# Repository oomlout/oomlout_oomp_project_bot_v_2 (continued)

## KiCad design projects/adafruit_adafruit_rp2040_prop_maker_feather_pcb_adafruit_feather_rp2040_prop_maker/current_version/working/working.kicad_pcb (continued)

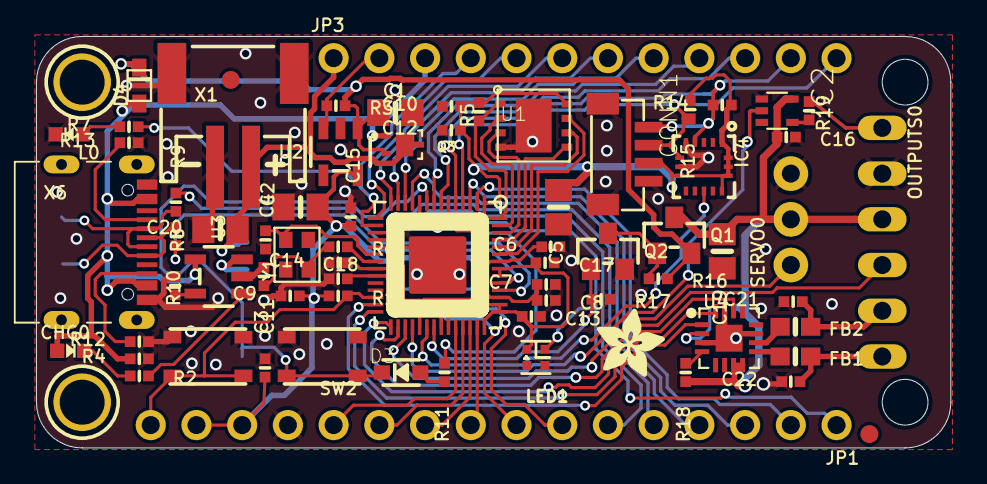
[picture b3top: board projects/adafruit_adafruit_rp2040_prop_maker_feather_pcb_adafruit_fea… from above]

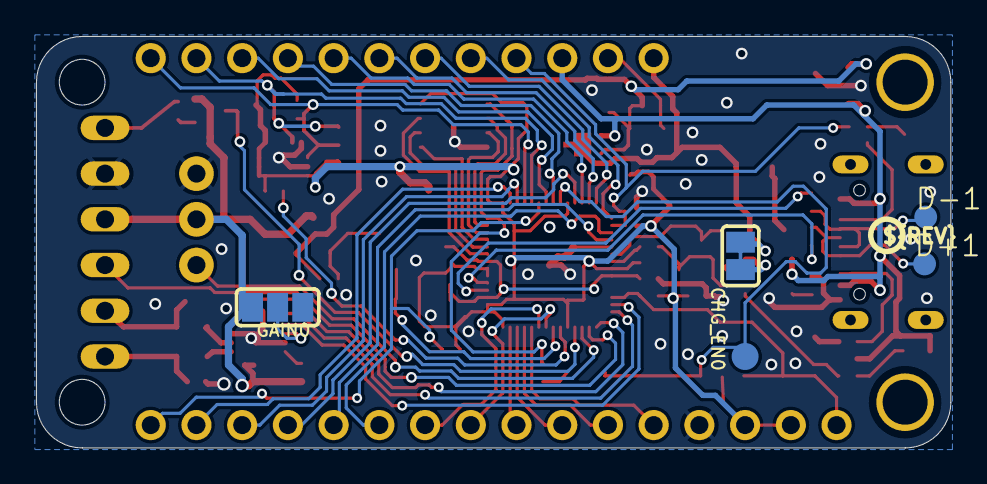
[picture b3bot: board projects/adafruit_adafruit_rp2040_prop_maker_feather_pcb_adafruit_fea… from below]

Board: 2 copper layers, 50.8 x 22.9 mm, 164 parts (51 on the bottom side), 69 nets.

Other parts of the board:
@HOLE0, @HOLE1: (no value)
PLABEL0: PLABEL0
PLABEL1: PLABEL1
PLABEL2: PLABEL2
PLABEL3: PLABEL3
PLABEL4: PLABEL4
PLABEL5: PLABEL5
PLABEL6: PLABEL6
PLABEL7: PLABEL7
PLABEL8: PLABEL8
PLABEL9: PLABEL9
PLABEL10: PLABEL10
PLABEL11: PLABEL11
PLABEL12: PLABEL12
PLABEL13: PLABEL13
PLABEL14: PLABEL14
PLABEL15: PLABEL15
PLABEL16: PLABEL16
PLABEL17: PLABEL17
PLABEL18: PLABEL18
PLABEL19, PLABEL26: PLABEL26
PLABEL21: PLABEL21
PLABEL22: PLABEL22
PLABEL23: PLABEL23
PLABEL24: PLABEL24
PLABEL25: PLABEL25
PLABEL27: PLABEL27
PLABEL28: PLABEL28
PLABEL29: PLABEL29
PLABEL30: PLABEL30
PLABEL31: PLABEL31
PLABEL32: PLABEL32
PLABEL33: PLABEL33
PLABEL36: PLABEL36
PLABEL37: PLABEL37
PLABEL38: PLABEL38
PLABEL39: PLABEL39
PLABEL40: PLABEL40
PLABEL41: PLABEL41
PLABEL42: PLABEL42
PLABEL43: PLABEL43
PLABEL44: PLABEL44
PLABEL45: PLABEL45
PLABEL46: PLABEL46
PLABEL47: PLABEL47
PLABEL48: PLABEL48
PLABEL49: PLABEL49
PLABEL50: PLABEL50
PLABEL51: PLABEL51
PLABEL52: PLABEL52
PLABEL53: PLABEL53
PLABEL54: PLABEL54
PLABEL55: PLABEL55
PLABEL56: PLABEL56
PLABEL57: PLABEL57
PLABEL58: PLABEL58
PLABEL59: PLABEL59
PLABEL60: PLABEL60
PLABEL61: PLABEL61
PLABEL62: PLABEL62
PLABEL63: PLABEL63
PLABEL68: PLABEL68
PLABEL69: PLABEL69
PLABEL70: PLABEL70
PLABEL71: PLABEL71
PLABEL72: PLABEL72
PLABEL73: PLABEL73
PLABEL74: PLABEL74
PLABEL75: PLABEL75
PLABEL76: PLABEL76
PLABEL77: PLABEL77
PLABEL78: PLABEL78
PLABEL79: PLABEL79
PLABEL80: PLABEL80
PLABEL81: PLABEL81
PLABEL82: PLABEL82
PLABEL83: PLABEL83
PLABEL84: PLABEL84
PLABEL85: PLABEL85
PLABEL86: PLABEL86
PLABEL87: PLABEL87
PLABEL88: PLABEL88
PLABEL89: PLABEL89
U$13: PCBFEAT-REV-040
U$42: ADAFRUIT_3.5MM

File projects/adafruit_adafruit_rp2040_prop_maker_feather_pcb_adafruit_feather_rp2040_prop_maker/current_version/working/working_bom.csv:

"Id";"Designator";"Footprint";"Quantity";"Designation";"Supplier and ref";
1;"PLABEL30";"PLABEL30";1;"";;;
2;"R2,R5,R1,R4,R14,R3,R15,R7";"_0402NO";8;"10K";;;
3;"C7,C6,C12,C18,C9,C13,C16,C14";"_0402NO";8;"0.1uF";;;
4;"R6,R11";"_0402NO";2;"1K";;;
5;"U$31,U$32";"MOUNTINGHOLE_2.5_PLATED";2;"MOUNTINGHOLE2.5";;;
6;"C20,C1,C19,C5,C4";"0805-NO";5;"10uF/16V";;;
7;"PLABEL72";"PLABEL72";1;"";;;
8;"U$35,U$34";"FIDUCIAL_1MM";2;"FIDUCIAL_1MM";;;
9;"OUTPUTS0";"1X06_OVAL";1;"TERMINALS";;;
10;"PLABEL13";"PLABEL13";1;"";;;
11;"LED1";"SK6805_1515";1;"WS2812B_SK6805_1515";;;
12;"PLABEL73";"PLABEL73";1;"";;;
13;"R19";"_0402NO";1;"100";;;
14;"PLABEL6";"PLABEL6";1;"";;;
15;"Y1";"CRYSTAL_2.5X2";1;"12MHz/12pF";;;
16;"PLABEL33";"PLABEL33";1;"";;;
17;"U2";"SOT23-5";1;"RT9080-3.3";;;
18;"R16,R17";"_0402NO";2;"100K";;;
19;"PLABEL19,PLABEL26";"PLABEL26";2;"";;;
20;"PLABEL36";"PLABEL36";1;"";;;
21;"PLABEL23";"PLABEL23";1;"";;;
22;"C2,C3";"_0402NO";2;"22pF";;;
23;"C10,C11,C15,C8,C17";"_0402NO";5;"1uF/25V";;;
24;"SERVO0";"1X03_ROUND_76";1;"1x3M";;;
25;"IC1";"QFN56_7MM_REDUCEDEPAD";1;"RP2040_QFN56";;;
26;"R12,R8,R13";"_0402NO";3;"5.1K";;;
27;"PLABEL18";"PLABEL18";1;"";;;
28;"R18";"_0402NO";1;"1M";;;
29;"PLABEL5";"PLABEL5";1;"";;;
30;"@HOLE1,@HOLE0";"";2;"";;;
31;"PLABEL16";"PLABEL16";1;"";;;
32;"PLABEL3";"PLABEL3";1;"";;;
33;"PLABEL4";"PLABEL4";1;"";;;
34;"U3";"SOT23-5";1;"MCP73831T-2ACI/OT";;;
35;"PLABEL27";"PLABEL27";1;"";;;
36;"PLABEL17";"PLABEL17";1;"";;;
37;"IC4";"LGA16_3X3MM";1;"LIS3DH";;;
38;"R10,R9";"_0402NO";2;"22 ohm";;;
39;"C22,C21";"_0402NO";2;"220pF";;;
40;"PLABEL22";"PLABEL22";1;"";;;
41;"U4";"QFN16_3MM";1;"MAX98357A";;;
42;"X6";"USB_C_CUSB31-CFM2AX-01-X";1;"USB Type C";;;
43;"PLABEL71";"PLABEL71";1;"";;;
44;"L0";"CHIPLED_0603_NOOUTLINE";1;"RED";;;
45;"PLABEL21";"PLABEL21";1;"";;;
46;"PLABEL31";"PLABEL31";1;"";;;
47;"PLABEL7";"PLABEL7";1;"";;;
48;"PLABEL12";"PLABEL12";1;"";;;
49;"PLABEL8";"PLABEL8";1;"";;;
50;"Q2";"SOT23-WIDE";1;"C20917";;;
51;"PLABEL9";"PLABEL9";1;"";;;
52;"Q1";"SOT23-WIDE";1;"AO3401";;;
53;"Q3";"DFN2015-3";1;"DMG3415UFY";;;
54;"FB2,FB1";"0603-NO";2;"Ferrite";;;
55;"PLABEL2";"PLABEL2";1;"";;;
56;"PLABEL24";"PLABEL24";1;"";;;
57;"PLABEL11";"PLABEL11";1;"";;;
58;"SW2,SW1";"BTN_RKB2_4.6X2.8";2;"RKB2";;;
59;"U1";"USON8_4X4";1;"8MB QSPI";;;
60;"PLABEL10";"PLABEL10";1;"";;;
61;"PLABEL28";"PLABEL28";1;"";;;
62;"X1";"JSTPH2_BATT";1;"JSTPH";;;
63;"PLABEL29";"PLABEL29";1;"";;;
64;"U$42";"ADAFRUIT_3.5MM";1;"";;;
65;"PLABEL14";"PLABEL14";1;"";;;
66;"CONN1";"JST_SH4_RA";1;"STEMMA_I2C_QTRA";;;
67;"JP3";"1X12_ROUND";1;"";;;
68;"D3";"SOD-323_MINI";1;"1N4148";;;
69;"D4";"SOD-323F";1;"PMEG2020AEA";;;
70;"PLABEL1";"PLABEL1";1;"";;;
71;"IC2";"SC70-5";1;"74AHCT1G125DCK";;;
72;"PLABEL25";"PLABEL25";1;"";;;
73;"JP1";"1X16_ROUND";1;"";;;
74;"PLABEL70";"PLABEL70";1;"";;;
75;"PLABEL32";"PLABEL32";1;"";;;
76;"PLABEL15";"PLABEL15";1;"";;;
77;"PLABEL0";"PLABEL0";1;"";;;
78;"CHG0";"CHIPLED_0603_NOOUTLINE";1;"ORANGE";;;
79;"PLABEL81";"PLABEL81";1;"";;;
80;"PLABEL88";"PLABEL88";1;"";;;
81;"PLABEL47";"PLABEL47";1;"";;;
82;"PLABEL75";"PLABEL75";1;"";;;
83;"PLABEL69";"PLABEL69";1;"";;;
84;"PLABEL50";"PLABEL50";1;"";;;
85;"PLABEL40";"PLABEL40";1;"";;;
86;"PLABEL51";"PLABEL51";1;"";;;
87;"PLABEL42";"PLABEL42";1;"";;;
88;"PLABEL46";"PLABEL46";1;"";;;
89;"PLABEL86";"PLABEL86";1;"";;;
90;"PLABEL60";"PLABEL60";1;"";;;
91;"U$13";"PCBFEAT-REV-040";1;"";;;
92;"D+1,D-1";"B1,27";2;"TPB1,27";;;
93;"PLABEL38";"PLABEL38";1;"";;;
94;"PLABEL58";"PLABEL58";1;"";;;
95;"PLABEL55";"PLABEL55";1;"";;;
96;"PLABEL85";"PLABEL85";1;"";;;
97;"PLABEL59";"PLABEL59";1;"";;;
98;"GAIN0";"SOLDERJUMPER_2WAY_OPEN_NOPASTE";1;"";;;
99;"PLABEL82";"PLABEL82";1;"";;;
100;"PLABEL80";"PLABEL80";1;"";;;
101;"PLABEL57";"PLABEL57";1;"";;;
102;"PLABEL45";"PLABEL45";1;"";;;
103;"PLABEL48";"PLABEL48";1;"";;;
104;"PLABEL52";"PLABEL52";1;"";;;
105;"PLABEL77";"PLABEL77";1;"";;;
106;"TP3";"TESTPOINT_ROUND_1.5MM_NO";1;"";;;
107;"PLABEL43";"PLABEL43";1;"";;;
108;"PLABEL53";"PLABEL53";1;"";;;
109;"PLABEL62";"PLABEL62";1;"";;;
110;"PLABEL83";"PLABEL83";1;"";;;
111;"PLABEL74";"PLABEL74";1;"";;;
112;"PLABEL41";"PLABEL41";1;"";;;
113;"PLABEL56";"PLABEL56";1;"";;;
114;"PLABEL76";"PLABEL76";1;"";;;
115;"PLABEL61";"PLABEL61";1;"";;;
116;"PLABEL78";"PLABEL78";1;"";;;
117;"PLABEL89";"PLABEL89";1;"";;;
118;"PLABEL37";"PLABEL37";1;"";;;
119;"PLABEL68";"PLABEL68";1;"";;;
120;"PLABEL39";"PLABEL39";1;"";;;
121;"PLABEL84";"PLABEL84";1;"";;;
122;"PLABEL54";"PLABEL54";1;"";;;
123;"PLABEL87";"PLABEL87";1;"";;;
124;"PLABEL63";"PLABEL63";1;"";;;
125;"PLABEL79";"PLABEL79";1;"";;;
126;"PLABEL49";"PLABEL49";1;"";;;
127;"PLABEL44";"PLABEL44";1;"";;;
128;"CHG_EN0";"SOLDERJUMPER_CLOSEDWIRE";1;"";;;

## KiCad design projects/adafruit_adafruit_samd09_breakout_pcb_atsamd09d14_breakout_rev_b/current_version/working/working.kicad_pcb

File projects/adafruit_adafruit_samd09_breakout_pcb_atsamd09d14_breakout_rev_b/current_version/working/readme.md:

# adafruit_samd09_breakout_pcb
 
## summary 
* id: adafruit_adafruit_samd09_breakout_pcb_atsamd09d14_breakout_rev_b
* user: adafruit
* name: adafruit_samd09_breakout_pcb
* board: atsamd09d14_breakout_rev_b
* repo: https://github.com/adafruit/Adafruit-SAMD09-Breakout-PCB

* src_file_repo_sch: 
* src_file_repo_sch_link: https://github.com/adafruit/Adafruit-SAMD09-Breakout-PCB/tree/master/
* full details link: https://github.com/oomlout/oomlout_oomp_project_bot_v_2/tree/main/projects/adafruit_adafruit_samd09_breakout_pcb_atsamd09d14_breakout_rev_b/current_version/working  

## schematic  
  
[schematic (pdf)](working_schematic.pdf) 

## pcb  

[board (pdf)](working.pdf)  

## working_bom
| Id | Designator | Footprint | Quantity | Designation | Supplier and ref |  | None | 
| --- | --- | --- | --- | --- | --- | --- | --- | 
| 1 | JP3,JP1 | 1X12_ROUND_76MIL | 2 |  |  |  | [''] | 
| 2 | R4,R5 | 0603-NO | 2 | 10k |  |  | [''] | 
| 3 | U$12 | PCBFEAT-REV-040 | 1 |  |  |  | [''] | 
| 4 | IC1 | QFN24_4MM | 1 | ATSAMD09D14A-MU |  |  | [''] | 
| 5 | D2 | CHIPLED_0805_NOOUTLINE | 1 | GREEN |  |  | [''] | 
| 6 | C2 | 0603-NO | 1 | 0.1uF |  |  | [''] | 
| 7 | C1,C4 | 0805-NO | 2 | 10uF |  |  | [''] | 
| 8 | FID1,FID2 | FIDUCIAL_1MM | 2 | FIDUCIAL" |  |  | [''] | 
| 9 | SW1 | BTN_KMR2_4.6X2.8 | 1 | KMR2 |  |  | [''] | 
| 10 | R1,R2,R3 | 0603-NO | 3 | 1K |  |  | [''] | 
| 11 | D1 | CHIPLED_0805_NOOUTLINE | 1 | RED |  |  | [''] | 
| 12 | U1 | SOT23-5 | 1 | AP2112K |  |  | [''] | 
| 13 | U$7 | SEESAW_LOGO | 1 |  |  |  | [''] | 

## bom_schematic
| Ref | Qnty | Value | Cmp name | Footprint | Description | Vendor | DNP | 
| --- | --- | --- | --- | --- | --- | --- | --- | 
| C1, C4 | 2 | 10uF | CAP_CERAMIC0805-NOOUTLINE | working:0805-NO |  |  |  | 
| C2 | 1 | 0.1uF | CAP_CERAMIC0603_NO | working:0603-NO |  |  |  | 
| D1 | 1 | RED | LED0805_NOOUTLINE | working:CHIPLED_0805_NOOUTLINE |  |  |  | 
| D2 | 1 | GREEN | LED0805_NOOUTLINE | working:CHIPLED_0805_NOOUTLINE |  |  |  | 
| FID1, FID2 | 2 | FIDUCIAL"" | FIDUCIAL{dblquote}{dblquote} | working:FIDUCIAL_1MM |  |  |  | 
| IC1 | 1 | ATSAMD09D14A-MU | ATSAMD09D14A-MU | working:QFN24_4MM |  |  |  | 
| JP1, JP3 | 2 | HEADER-1X1276MIL | HEADER-1X1276MIL | working:1X12_ROUND_76MIL |  |  |  | 
| R1, R2, R3 | 3 | 1K | RESISTOR_0603_NOOUT | working:0603-NO |  |  |  | 
| R4, R5 | 2 | 10k | RESISTOR_0603_NOOUT | working:0603-NO |  |  |  | 
| SW1 | 1 | KMR2 | SWITCH_TACT_SMT4.6X2.8 | working:BTN_KMR2_4.6X2.8 |  |  |  | 
| U1 | 1 | AP2112K | VREG_SOT23-5 | working:SOT23-5 |  |  |  |

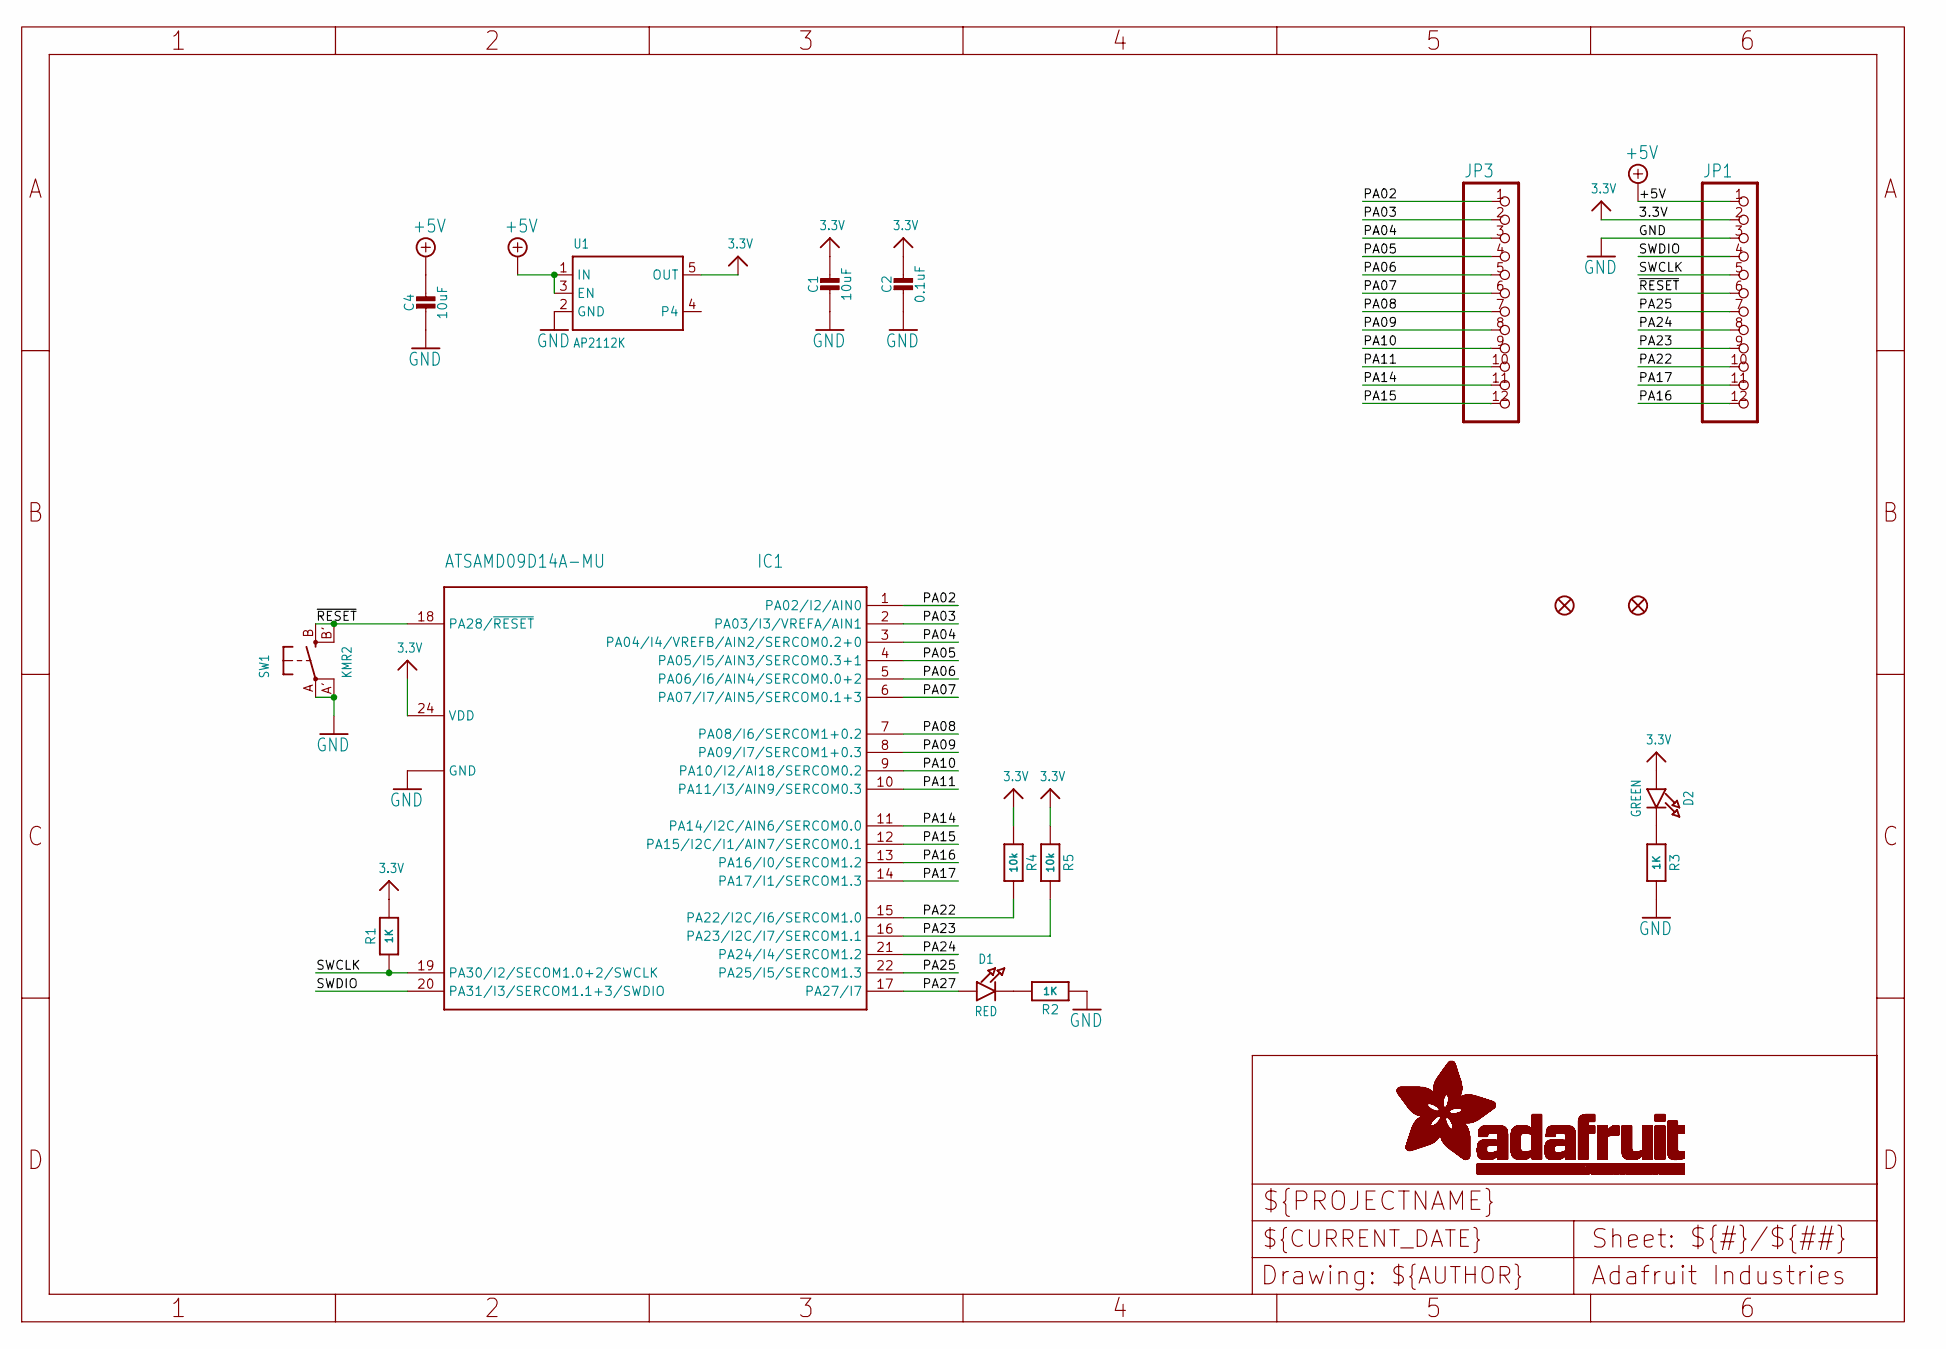
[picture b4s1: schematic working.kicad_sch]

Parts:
C1, C4: 10uF; 0805-NO
C2: 0.1uF; 0603-NO
D1: RED; CHIPLED_0805_NOOUTLINE
D2: GREEN; CHIPLED_0805_NOOUTLINE
FID1, FID2: FIDUCIAL""; FIDUCIAL_1MM
IC1: ATSAMD09D14A-MU; QFN24_4MM
JP1, JP3: HEADER-1X1276MIL; 1X12_ROUND_76MIL
R1, R2, R3: 1K; 0603-NO
R4, R5: 10k; 0603-NO
SW1: KMR2; BTN_KMR2_4.6X2.8
U1: AP2112K; SOT23-5

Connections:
3.3V: C1.1, C2.1, D2.A, IC1.24 (VDD), JP1.2, R1.2, R4.1, R5.1, U1.5 (OUT)
+5V: C4.1, JP1.1, U1.1 (IN), U1.3 (EN)
GND: C1.2, C2.2, C4.2, IC1.23 (GND), IC1.THERM (GND), JP1.3, R2.1, R3.2, SW1.A, SW1.A' (P1), U1.2 (GND)
unnamed: D1.C, R2.2
unnamed: D2.C, R3.1
PA02: IC1.1 (PA02/I2/AIN0), JP3.1
PA03: IC1.2 (PA03/I3/VREFA/AIN1), JP3.2
PA04: IC1.3 (PA04/I4/VREFB/AIN2/SERCOM0.2+0), JP3.3
PA05: IC1.4 (PA05/I5/AIN3/SERCOM0.3+1), JP3.4
PA06: IC1.5 (PA06/I6/AIN4/SERCOM0.0+2), JP3.5
PA07: IC1.6 (PA07/I7/AIN5/SERCOM0.1+3), JP3.6
PA08: IC1.7 (PA08/I6/SERCOM1+0.2), JP3.7
PA09: IC1.8 (PA09/I7/SERCOM1+0.3), JP3.8
PA10: IC1.9 (PA10/I2/AI18/SERCOM0.2), JP3.9
PA11: IC1.10 (PA11/I3/AIN9/SERCOM0.3), JP3.10
PA14: IC1.11 (PA14/I2C/AIN6/SERCOM0.0), JP3.11
PA15: IC1.12 (PA15/I2C/I1/AIN7/SERCOM0.1), JP3.12
PA16: IC1.13 (PA16/I0/SERCOM1.2), JP1.12
PA17: IC1.14 (PA17/I1/SERCOM1.3), JP1.11
PA22: IC1.15 (PA22/I2C/I6/SERCOM1.0), JP1.10, R4.2
PA23: IC1.16 (PA23/I2C/I7/SERCOM1.1), JP1.9, R5.2
PA24: IC1.21 (PA24/I4/SERCOM1.2), JP1.8
PA25: IC1.22 (PA25/I5/SERCOM1.3), JP1.7
PA27: D1.A, IC1.17 (PA27/I7)
SWCLK: IC1.19 (PA30/I2/SECOM1.0+2/SWCLK), JP1.5, R1.1
SWDIO: IC1.20 (PA31/I3/SERCOM1.1+3/SWDIO), JP1.4
~RESET: IC1.18 (PA28/~RESET), JP1.6, SW1.B (S), SW1.B' (S1)

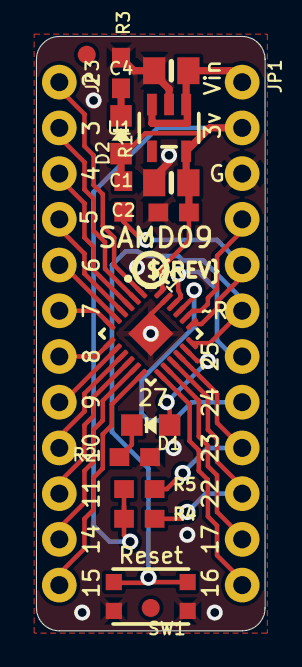
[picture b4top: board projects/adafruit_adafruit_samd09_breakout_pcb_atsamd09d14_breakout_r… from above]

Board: 2 copper layers, 12.7 x 33.0 mm, 19 parts (1 on the bottom side), 27 nets.

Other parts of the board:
U$7: SEESAW_LOGO
U$12: PCBFEAT-REV-040

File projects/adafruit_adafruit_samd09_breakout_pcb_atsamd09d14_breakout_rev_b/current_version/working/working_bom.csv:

"Id";"Designator";"Footprint";"Quantity";"Designation";"Supplier and ref";
1;"JP3,JP1";"1X12_ROUND_76MIL";2;"";;;
2;"R4,R5";"0603-NO";2;"10k";;;
3;"U$12";"PCBFEAT-REV-040";1;"";;;
4;"IC1";"QFN24_4MM";1;"ATSAMD09D14A-MU";;;
5;"D2";"CHIPLED_0805_NOOUTLINE";1;"GREEN";;;
6;"C2";"0603-NO";1;"0.1uF";;;
7;"C1,C4";"0805-NO";2;"10uF";;;
8;"FID1,FID2";"FIDUCIAL_1MM";2;"FIDUCIAL""";;;
9;"SW1";"BTN_KMR2_4.6X2.8";1;"KMR2";;;
10;"R1,R2,R3";"0603-NO";3;"1K";;;
11;"D1";"CHIPLED_0805_NOOUTLINE";1;"RED";;;
12;"U1";"SOT23-5";1;"AP2112K";;;
13;"U$7";"SEESAW_LOGO";1;"";;;

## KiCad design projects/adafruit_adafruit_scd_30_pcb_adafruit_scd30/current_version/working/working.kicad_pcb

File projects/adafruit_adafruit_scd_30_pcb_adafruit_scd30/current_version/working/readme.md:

# adafruit_scd_30_pcb
 
## summary 
* id: adafruit_adafruit_scd_30_pcb_adafruit_scd30
* user: adafruit
* name: adafruit_scd_30_pcb
* board: adafruit_scd30
* repo: https://github.com/adafruit/Adafruit-SCD-30-PCB

* src_file_repo_sch: 
* src_file_repo_sch_link: https://github.com/adafruit/Adafruit-SCD-30-PCB/tree/main/
* full details link: https://github.com/oomlout/oomlout_oomp_project_bot_v_2/tree/main/projects/adafruit_adafruit_scd_30_pcb_adafruit_scd30/current_version/working  

## schematic  
  
[schematic (pdf)](working_schematic.pdf) 

## pcb  

[board (pdf)](working.pdf)  

## working_bom
| Id | Designator | Footprint | Quantity | Designation | Supplier and ref |  | None | 
| --- | --- | --- | --- | --- | --- | --- | --- | 
| 1 | CONN4,CONN3 | JST_SH4 | 2 | STEMMA_I2C_QT |  |  | [''] | 
| 2 | C1 | 0603-NO | 1 | 0.1uF |  |  | [''] | 
| 3 | R1 | 0603-NO | 1 | 10K |  |  | [''] | 
| 4 | X1 | SCD30 | 1 | SCD30 |  |  | [''] | 
| 5 | C2,C3 | 0805-NO | 2 | 10uF |  |  | [''] | 
| 6 | U$22 | ADAFRUIT_3.5MM | 1 |  |  |  | [''] | 
| 7 | JP1 | 1X06_ROUND_70 | 1 |  |  |  | [''] | 
| 8 | U2 | SOT23-5 | 1 | AP2112K-3.3 |  |  | [''] | 
| 9 | U$17,U$21,U$19,U$1 | MOUNTINGHOLE_2.5_PLATED | 4 | MOUNTINGHOLE2.5 |  |  | [''] | 
| 10 | Q2 | SOT363 | 1 | BSS138 |  |  | [''] | 
| 11 | FID4,FID3 | FIDUCIAL_1MM | 2 | FIDUCIAL_1MM |  |  | [''] | 
| 12 | R3 | RESPACK_4X0603 | 1 | 10K |  |  | [''] | 
| 13 | D1 | CHIPLED_0603_NOOUTLINE | 1 | GREEN |  |  | [''] | 
| 14 | U$30 | STEMMAQT | 1 |  |  |  | [''] | 
| 15 | U$25 | PCBFEAT-REV-040 | 1 |  |  |  | [''] | 

## bom_schematic
| Ref | Qnty | Value | Cmp name | Footprint | Description | Vendor | DNP | 
| --- | --- | --- | --- | --- | --- | --- | --- | 
| C1 | 1 | 0.1uF | CAP_CERAMIC0603_NO | working:0603-NO |  |  |  | 
| C2, C3 | 2 | 10uF | CAP_CERAMIC0805-NOOUTLINE | working:0805-NO |  |  |  | 
| CONN3, CONN4 | 2 | STEMMA_I2C_QT | STEMMA_I2C_QT | working:JST_SH4 |  |  |  | 
| D1 | 1 | GREEN | LED0603_NOOUTLINE | working:CHIPLED_0603_NOOUTLINE |  |  |  | 
| FID3, FID4 | 2 | FIDUCIAL_1MM | FIDUCIAL_1MM | working:FIDUCIAL_1MM |  |  |  | 
| JP1 | 1 | HEADER-1X670MIL | HEADER-1X670MIL | working:1X06_ROUND_70 |  |  |  | 
| Q2 | 1 | BSS138 | MOSFET-N_DUAL | working:SOT363 |  |  |  | 
| R1 | 1 | 10K | RESISTOR_0603_NOOUT | working:0603-NO |  |  |  | 
| R3 | 1 | 10K | RESISTOR_4PACK | working:RESPACK_4X0603 |  |  |  | 
| U2 | 1 | AP2112K-3.3 | VREG_SOT23-5 | working:SOT23-5 |  |  |  | 
| U$1, U$17, U$19, U$21 | 4 | MOUNTINGHOLE2.5 | MOUNTINGHOLE2.5 | working:MOUNTINGHOLE_2.5_PLATED |  |  |  | 
| X1 | 1 | SCD30 | SCD30 | working:SCD30 |  |  |  | 

## mounting_holes
| x | y | package | value | ref | size | 
| --- | --- | --- | --- | --- | --- | 
| 0.0 | 20.32 | MOUNTINGHOLE_2.5_PLATED | MOUNTINGHOLE2.5 | U$1 | m3 | 
| 45.72 | 20.32 | MOUNTINGHOLE_2.5_PLATED | MOUNTINGHOLE2.5 | U$17 | m3 | 
| 0.0 | 0.0 | MOUNTINGHOLE_2.5_PLATED | MOUNTINGHOLE2.5 | U$19 | m3 | 
| 45.72 | 0.0 | MOUNTINGHOLE_2.5_PLATED | MOUNTINGHOLE2.5 | U$21 | m3 |

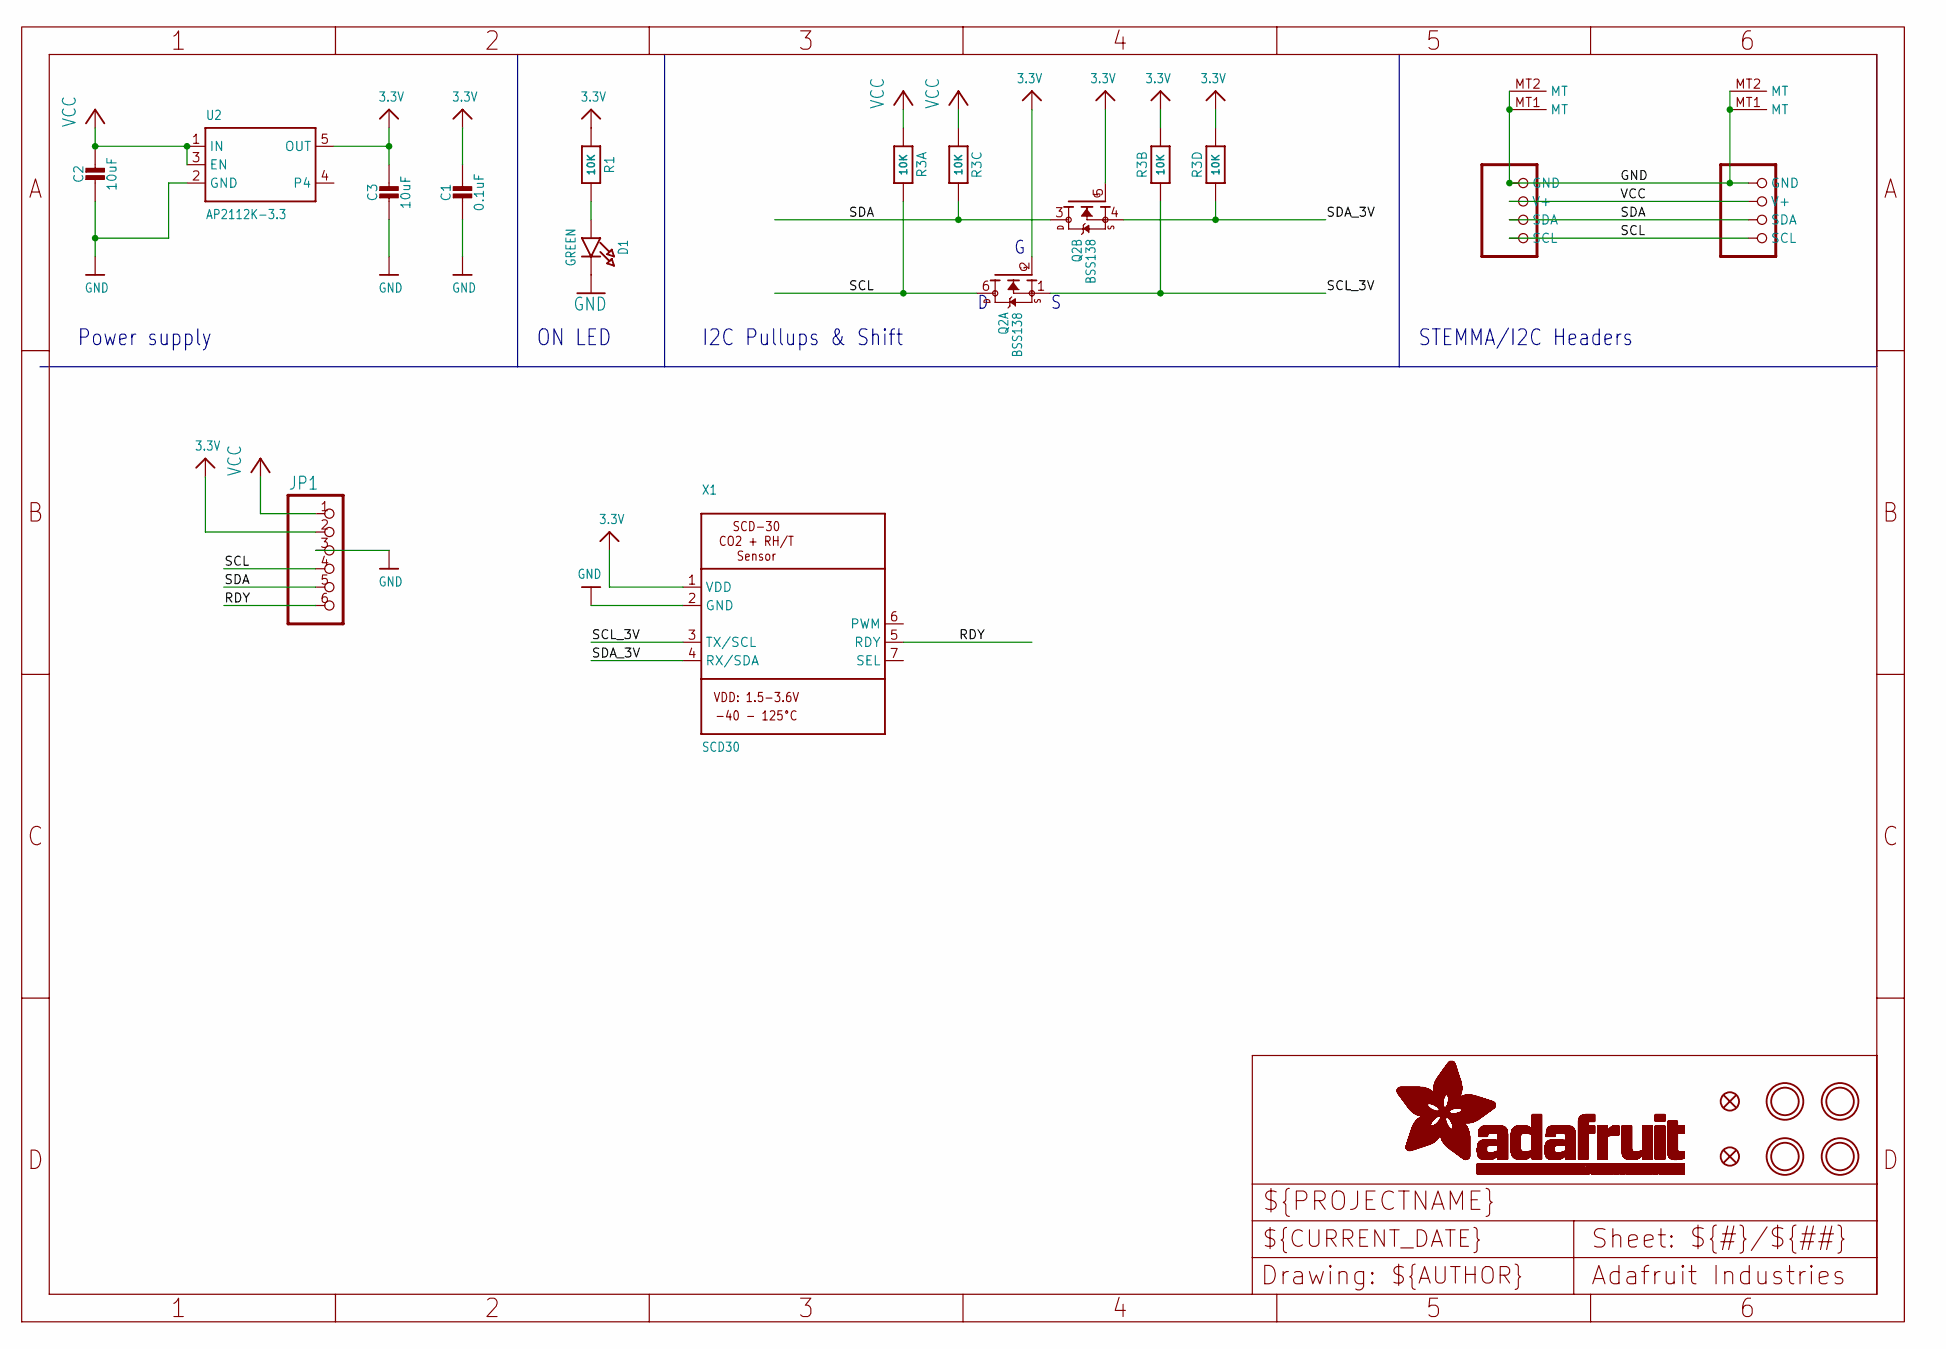
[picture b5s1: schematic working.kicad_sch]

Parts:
C1: 0.1uF; 0603-NO
C2, C3: 10uF; 0805-NO
CONN3, CONN4: STEMMA_I2C_QT; JST_SH4
D1: GREEN; CHIPLED_0603_NOOUTLINE
FID3, FID4: FIDUCIAL_1MM
JP1: HEADER-1X670MIL; 1X06_ROUND_70
Q2: BSS138; SOT363
R1: 10K; 0603-NO
R3: 10K; RESPACK_4X0603
U2: AP2112K-3.3; SOT23-5
U$1, U$17, U$19, U$21: MOUNTINGHOLE2.5; MOUNTINGHOLE_2.5_PLATED
X1: SCD30

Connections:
3.3V: C1.1, C3.1, JP1.2, Q2.2 (G), Q2.5 (G), R1.1, R3.2 (1), R3.4 (1), U2.5 (OUT), X1.1 (VDD)
GND: C1.2, C2.2, C3.2, CONN3.1 (GND), CONN3.MT1 (MT), CONN3.MT2 (MT), CONN4.1 (GND), CONN4.MT1 (MT), CONN4.MT2 (MT), D1.C, JP1.3, U2.2 (GND), X1.2 (GND)
unnamed: D1.A, R1.2
RDY: JP1.6, X1.5 (RDY)
SCL: CONN3.4 (SCL), CONN4.4 (SCL), JP1.4, Q2.6 (D), R3.8 (2)
SCL_3V: Q2.1 (S), R3.7 (2), X1.3 (TX/SCL)
SDA: CONN3.3 (SDA), CONN4.3 (SDA), JP1.5, Q2.3 (D), R3.6 (2)
SDA_3V: Q2.4 (S), R3.5 (2), X1.4 (RX/SDA)
VCC: C2.1, CONN3.2 (V+), CONN4.2 (V+), JP1.1, R3.1, R3.3 (1), U2.1 (IN), U2.3 (EN)

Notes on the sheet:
I2C Pullups & Shift
ON LED
STEMMA/I2C Headers
Power supply

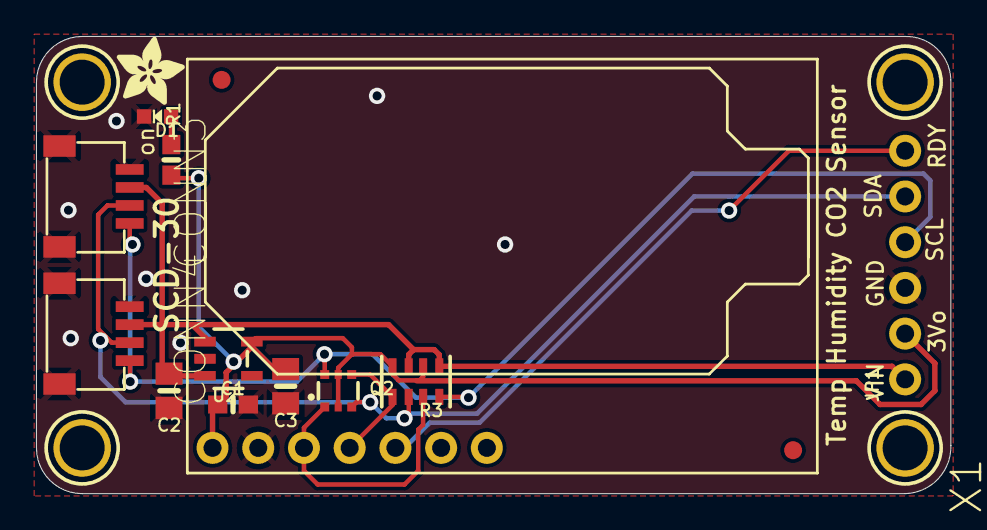
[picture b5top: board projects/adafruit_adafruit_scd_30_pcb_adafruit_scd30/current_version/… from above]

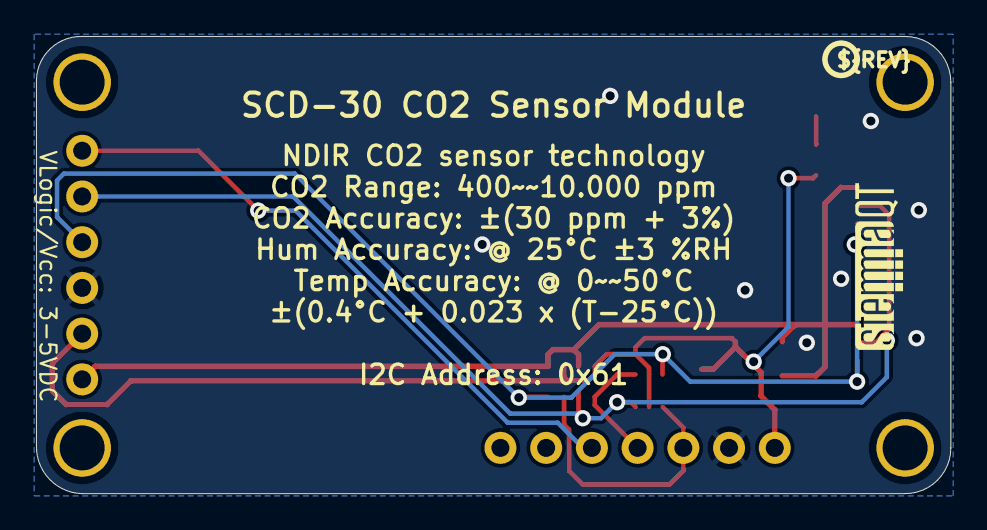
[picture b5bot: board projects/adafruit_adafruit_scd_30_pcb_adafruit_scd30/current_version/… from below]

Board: 2 copper layers, 50.8 x 25.4 mm, 21 parts (2 on the bottom side), 9 nets.

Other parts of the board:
U$22: ADAFRUIT_3.5MM
U$25: PCBFEAT-REV-040
U$30: STEMMAQT

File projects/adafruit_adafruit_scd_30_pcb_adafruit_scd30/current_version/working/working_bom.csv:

"Id";"Designator";"Footprint";"Quantity";"Designation";"Supplier and ref";
1;"CONN4,CONN3";"JST_SH4";2;"STEMMA_I2C_QT";;;
2;"C1";"0603-NO";1;"0.1uF";;;
3;"R1";"0603-NO";1;"10K";;;
4;"X1";"SCD30";1;"SCD30";;;
5;"C2,C3";"0805-NO";2;"10uF";;;
6;"U$22";"ADAFRUIT_3.5MM";1;"";;;
7;"JP1";"1X06_ROUND_70";1;"";;;
8;"U2";"SOT23-5";1;"AP2112K-3.3";;;
9;"U$17,U$21,U$19,U$1";"MOUNTINGHOLE_2.5_PLATED";4;"MOUNTINGHOLE2.5";;;
10;"Q2";"SOT363";1;"BSS138";;;
11;"FID4,FID3";"FIDUCIAL_1MM";2;"FIDUCIAL_1MM";;;
12;"R3";"RESPACK_4X0603";1;"10K";;;
13;"D1";"CHIPLED_0603_NOOUTLINE";1;"GREEN";;;
14;"U$30";"STEMMAQT";1;"";;;
15;"U$25";"PCBFEAT-REV-040";1;"";;;

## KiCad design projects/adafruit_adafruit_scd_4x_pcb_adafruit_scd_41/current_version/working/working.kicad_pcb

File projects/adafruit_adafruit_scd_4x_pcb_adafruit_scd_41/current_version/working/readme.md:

# adafruit_scd_4x_pcb
 
## summary 
* id: adafruit_adafruit_scd_4x_pcb_adafruit_scd_41
* user: adafruit
* name: adafruit_scd_4x_pcb
* board: adafruit_scd_41
* repo: https://github.com/adafruit/Adafruit-SCD-4x-PCB

* src_file_repo_sch: 
* src_file_repo_sch_link: https://github.com/adafruit/Adafruit-SCD-4x-PCB/tree/main/
* full details link: https://github.com/oomlout/oomlout_oomp_project_bot_v_2/tree/main/projects/adafruit_adafruit_scd_4x_pcb_adafruit_scd_41/current_version/working  

## schematic  
  
[schematic (pdf)](working_schematic.pdf) 

## pcb  

[board (pdf)](working.pdf)  

## working_bom
| Id | Designator | Footprint | Quantity | Designation | Supplier and ref |  | None | 
| --- | --- | --- | --- | --- | --- | --- | --- | 
| 1 | U$1,U$19,U$21,U$17 | MOUNTINGHOLE_3.0_PLATEDTHIN | 4 | MOUNTINGHOLE3.0THIN |  |  | [''] | 
| 2 | U2 | SOT23-5 | 1 | AP2112K-3.3 |  |  | [''] | 
| 3 | JP2 | 1X05_ROUND_76 | 1 |  |  |  | [''] | 
| 4 | C1,C5 | 0603-NO | 2 | 0.1uF |  |  | [''] | 
| 5 | C2,C4,C3 | 0805-NO | 3 | 10uF |  |  | [''] | 
| 6 | CONN4,CONN3 | JST_SH4 | 2 | STEMMA_I2C_QT |  |  | [''] | 
| 7 | R3 | RESPACK_4X0603 | 1 | 10K |  |  | [''] | 
| 8 | SJ3 | SOLDERJUMPER_CLOSEDWIRE | 1 |  |  |  | [''] | 
| 9 | FID3,FID4 | FIDUCIAL_1MM | 2 | FIDUCIAL_1MM |  |  | [''] | 
| 10 | Q2 | SOT363 | 1 | BSS138 |  |  | [''] | 
| 11 | R1 | 0603-NO | 1 | 10K |  |  | [''] | 
| 12 | X1 | SCD41 | 1 | SCD-41 |  |  | [''] | 
| 13 | D1 | CHIPLED_0603_NOOUTLINE | 1 | GREEN |  |  | [''] | 
| 14 | U$22 | ADAFRUIT_3.5MM | 1 |  |  |  | [''] | 
| 15 | U$30,U$31 | STEMMAQT | 2 |  |  |  | [''] | 
| 16 | SJ1,SJ2 | SOLDERJUMPER_2WAY_OPEN_NOPASTE | 2 |  |  |  | [''] | 
| 17 | U$25 | PCBFEAT-REV-040 | 1 |  |  |  | [''] | 

## bom_schematic
| Ref | Qnty | Value | Cmp name | Footprint | Description | Vendor | DNP | 
| --- | --- | --- | --- | --- | --- | --- | --- | 
| C1, C5 | 2 | 0.1uF | CAP_CERAMIC0603_NO | working:0603-NO |  |  |  | 
| C2, C3, C4 | 3 | 10uF | CAP_CERAMIC0805-NOOUTLINE | working:0805-NO |  |  |  | 
| CONN3, CONN4 | 2 | STEMMA_I2C_QT | STEMMA_I2C_QT | working:JST_SH4 |  |  |  | 
| D1 | 1 | GREEN | LED0603_NOOUTLINE | working:CHIPLED_0603_NOOUTLINE |  |  |  | 
| FID3, FID4 | 2 | FIDUCIAL_1MM | FIDUCIAL_1MM | working:FIDUCIAL_1MM |  |  |  | 
| JP2 | 1 | HEADER-1X576MIL | HEADER-1X576MIL | working:1X05_ROUND_76 |  |  |  | 
| Q2 | 1 | BSS138 | MOSFET-N_DUAL | working:SOT363 |  |  |  | 
| R1 | 1 | 10K | RESISTOR_0603_NOOUT | working:0603-NO |  |  |  | 
| R3 | 1 | 10K | RESISTOR_4PACK | working:RESPACK_4X0603 |  |  |  | 
| SJ1, SJ2 | 2 | SOLDERJUMPER_2WAY | SOLDERJUMPER_2WAY | working:SOLDERJUMPER_2WAY_OPEN_NOPASTE |  |  |  | 
| SJ3 | 1 | SOLDERJUMPERCLOSED | SOLDERJUMPERCLOSED | working:SOLDERJUMPER_CLOSEDWIRE |  |  |  | 
| U2 | 1 | AP2112K-3.3 | VREG_SOT23-5 | working:SOT23-5 |  |  |  | 
| U$1, U$17, U$19, U$21 | 4 | MOUNTINGHOLE3.0THIN | MOUNTINGHOLE3.0THIN | working:MOUNTINGHOLE_3.0_PLATEDTHIN |  |  |  | 
| X1 | 1 | SCD-41 | SCD-41 | working:SCD41 |  |  |  | 

## mounting_holes
| x | y | package | value | ref | size | 
| --- | --- | --- | --- | --- | --- | 
| 0.0 | 17.78 | MOUNTINGHOLE_3.0_PLATEDTHIN | MOUNTINGHOLE3.0THIN | U$1 | m3 | 
| 20.32 | 17.78 | MOUNTINGHOLE_3.0_PLATEDTHIN | MOUNTINGHOLE3.0THIN | U$17 | m3 | 
| 0.0 | 0.0 | MOUNTINGHOLE_3.0_PLATEDTHIN | MOUNTINGHOLE3.0THIN | U$19 | m3 | 
| 20.32 | 0.0 | MOUNTINGHOLE_3.0_PLATEDTHIN | MOUNTINGHOLE3.0THIN | U$21 | m3 |

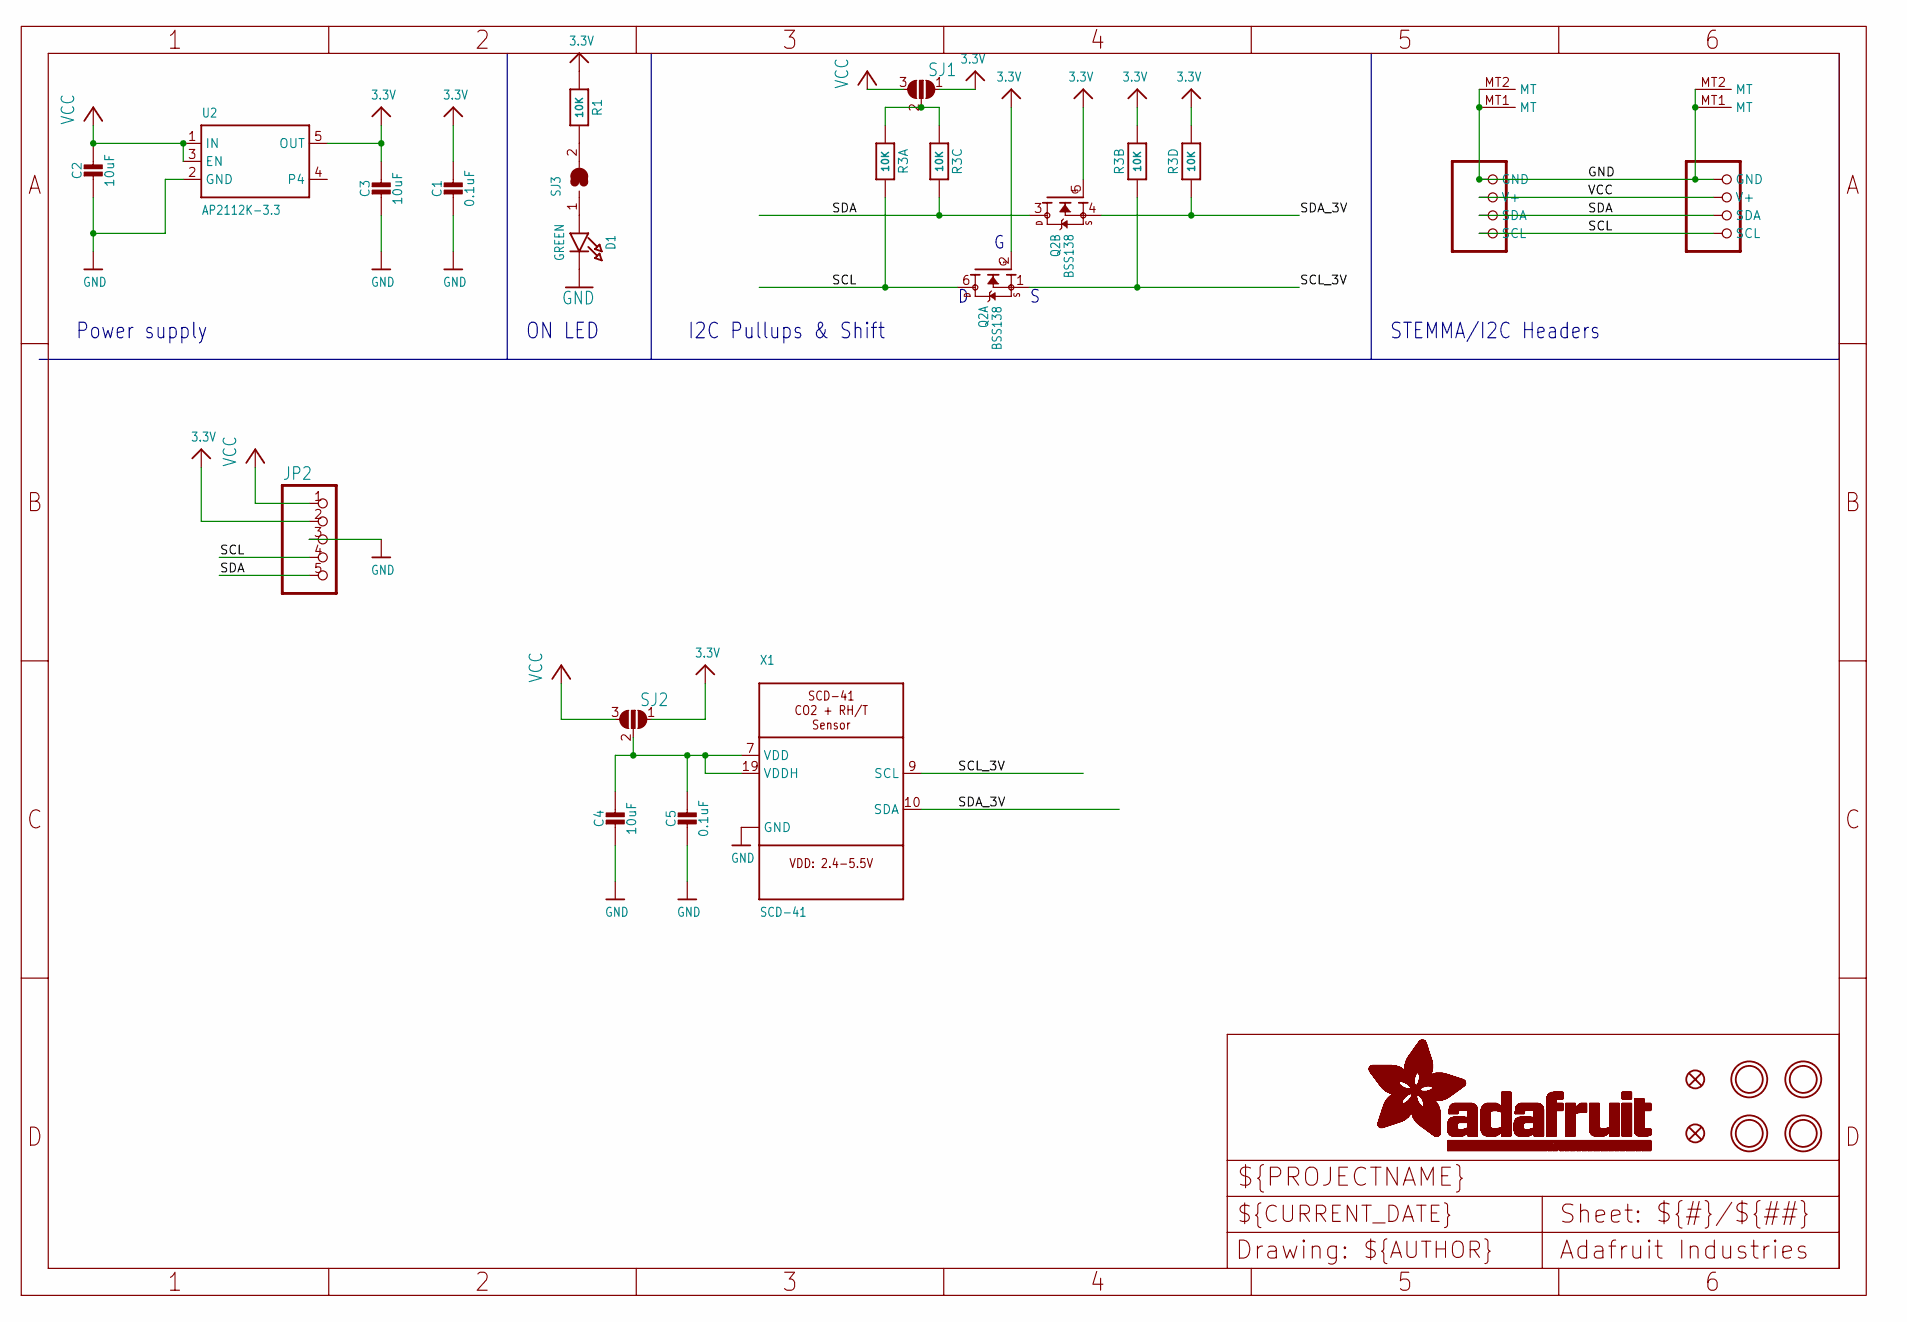
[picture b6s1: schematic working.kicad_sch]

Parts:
C1, C5: 0.1uF; 0603-NO
C2, C3, C4: 10uF; 0805-NO
CONN3, CONN4: STEMMA_I2C_QT; JST_SH4
D1: GREEN; CHIPLED_0603_NOOUTLINE
FID3, FID4: FIDUCIAL_1MM
JP2: HEADER-1X576MIL; 1X05_ROUND_76
Q2: BSS138; SOT363
R1: 10K; 0603-NO
R3: 10K; RESPACK_4X0603
SJ1, SJ2: SOLDERJUMPER_2WAY; SOLDERJUMPER_2WAY_OPEN_NOPASTE
SJ3: SOLDERJUMPERCLOSED; SOLDERJUMPER_CLOSEDWIRE
U2: AP2112K-3.3; SOT23-5
U$1, U$17, U$19, U$21: MOUNTINGHOLE3.0THIN; MOUNTINGHOLE_3.0_PLATEDTHIN
X1: SCD-41; SCD41

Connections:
3.3V: C1.1, C3.1, JP2.2, Q2.2 (G), Q2.5 (G), R1.1, R3.2 (1), R3.4 (1), SJ1.1, SJ2.1, U2.5 (OUT)
GND: C1.2, C2.2, C3.2, C4.2, C5.2, CONN3.1 (GND), CONN3.MT1 (MT), CONN3.MT2 (MT), CONN4.1 (GND), CONN4.MT1 (MT), CONN4.MT2 (MT), D1.C, JP2.3, U2.2 (GND), X1.6 (GND), X1.20 (GND), X1.P$1 (GND)
unnamed: D1.A, SJ3.1
unnamed: R3.1, R3.3 (1), SJ1.2
unnamed: C4.1, C5.1, SJ2.2, X1.7 (VDD), X1.19 (VDDH)
unnamed: R1.2, SJ3.2
SCL: CONN3.4 (SCL), CONN4.4 (SCL), JP2.4, Q2.6 (D), R3.8 (2)
SCL_3V: Q2.1 (S), R3.7 (2), X1.9 (SCL)
SDA: CONN3.3 (SDA), CONN4.3 (SDA), JP2.5, Q2.3 (D), R3.6 (2)
SDA_3V: Q2.4 (S), R3.5 (2), X1.10 (SDA)
VCC: C2.1, CONN3.2 (V+), CONN4.2 (V+), JP2.1, SJ1.3, SJ2.3, U2.1 (IN), U2.3 (EN)

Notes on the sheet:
I2C Pullups & Shift
ON LED
STEMMA/I2C Headers
Power supply

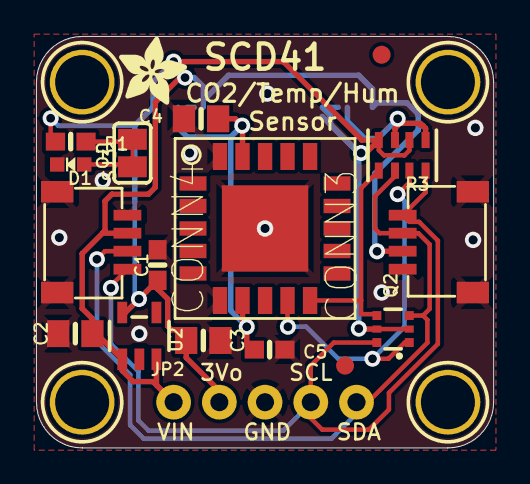
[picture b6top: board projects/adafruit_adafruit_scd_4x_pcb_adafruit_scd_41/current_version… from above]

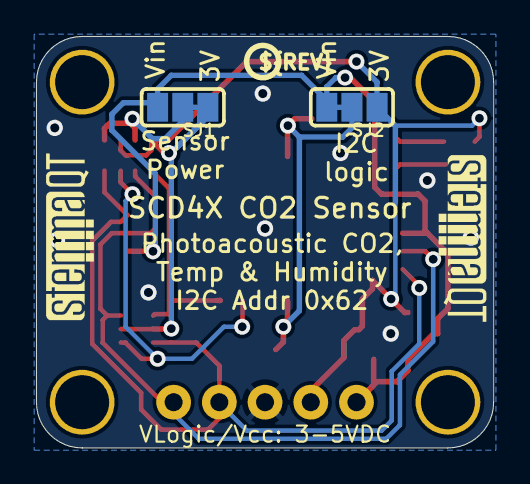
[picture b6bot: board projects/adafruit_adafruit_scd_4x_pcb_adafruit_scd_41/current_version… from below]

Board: 2 copper layers, 25.4 x 22.9 mm, 27 parts (5 on the bottom side), 11 nets.

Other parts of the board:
U$22: ADAFRUIT_3.5MM
U$25: PCBFEAT-REV-040
U$30, U$31: STEMMAQT
